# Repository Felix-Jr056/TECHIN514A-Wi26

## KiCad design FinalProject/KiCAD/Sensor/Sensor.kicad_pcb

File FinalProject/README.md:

# ErgoCompass
## Product Idea
ErgoCompass is a product that tracks how you sit using pressure sensors in the back pad and wirelessly sends the data to a desk display. The display converts your posture into a simple status on a physical gauge needle, with an LED alerts when you’ve been slouching for too long. A button on the display device allows calibrating and resets the session.

## Sensor Device
 The sensor device is composed of a fabric back pad with pressure sensors embedded in it. The sensors detect the pressure distribution when a user sits against the pad. The data from the sensors is collected by a microcontroller, which processes the information to determine the user's posture. The device is powered by a rechargeable battery and includes wireless communication capabilities to send the posture data to the desk display.

 Components used in the sensor device include:
 - Pressure Sensors: 3 FSRs (Force Sensitive Resistor).
 - Microcontroller: Custom PCB, may include FSR resistor network, status LED.
 - Wireless Module: For transmitting data to the display device (BLE).
 - Battery: Rechargeable LiPo battery with battery indicator.

| Component name | Model | Quantity |
|----------------|-------|----------|
| Force sensitive resistor | Interlink FSR 406 | 3 |
| Main microcontroller  | Custom PCB | 1 |
| BLE wireless module | Raytac MDBT42Q-512KV2 (nRF52832)| 1 |
| External ADC (optional) | TI ADS1115IDGSR | 1 |
| LiPo battery | 1S LiPo | 1 |
| Status LED | LS R976 | 1 |

## Display Device
The display device receives the posture data from the sensor device and translates it into a visual representation using a physical gauge needle. The needle moves to indicate whether the user's posture is good, moderate, or poor based on the pressure data received. Additionally, the display includes 3 LEDs that displays different colours serving as a pressure level indicator to correct user's posture. A button on the display allows users to calibrate the system and reset their session data.

Components used in the display device include:
- 1 Microcontroller: ESP32.
- 1 Stepper motor driven gauge needle: To visually represent the user's posture.
- 3 LEDs: Indicate the pressure level at each sensor.
- 1 Button: For calibration and session reset functionality.
 - 1 Battery: Small rechargeable LiPo battery.

| Component name | Model | Quantity |
|----------------|-------|----------|
| Microcontroller | XIAO ESP32-C3 | 1 |
| Stepper motor| 28BYJ-48 | 1 |
| LEDs | NeoPixel | 3 |
| Button | Omron B3U-1000P | 1 |
| LiPo battery | 1S LiPo  | 1 |

## Diagrams
### Communication chart

### System Block Diagram

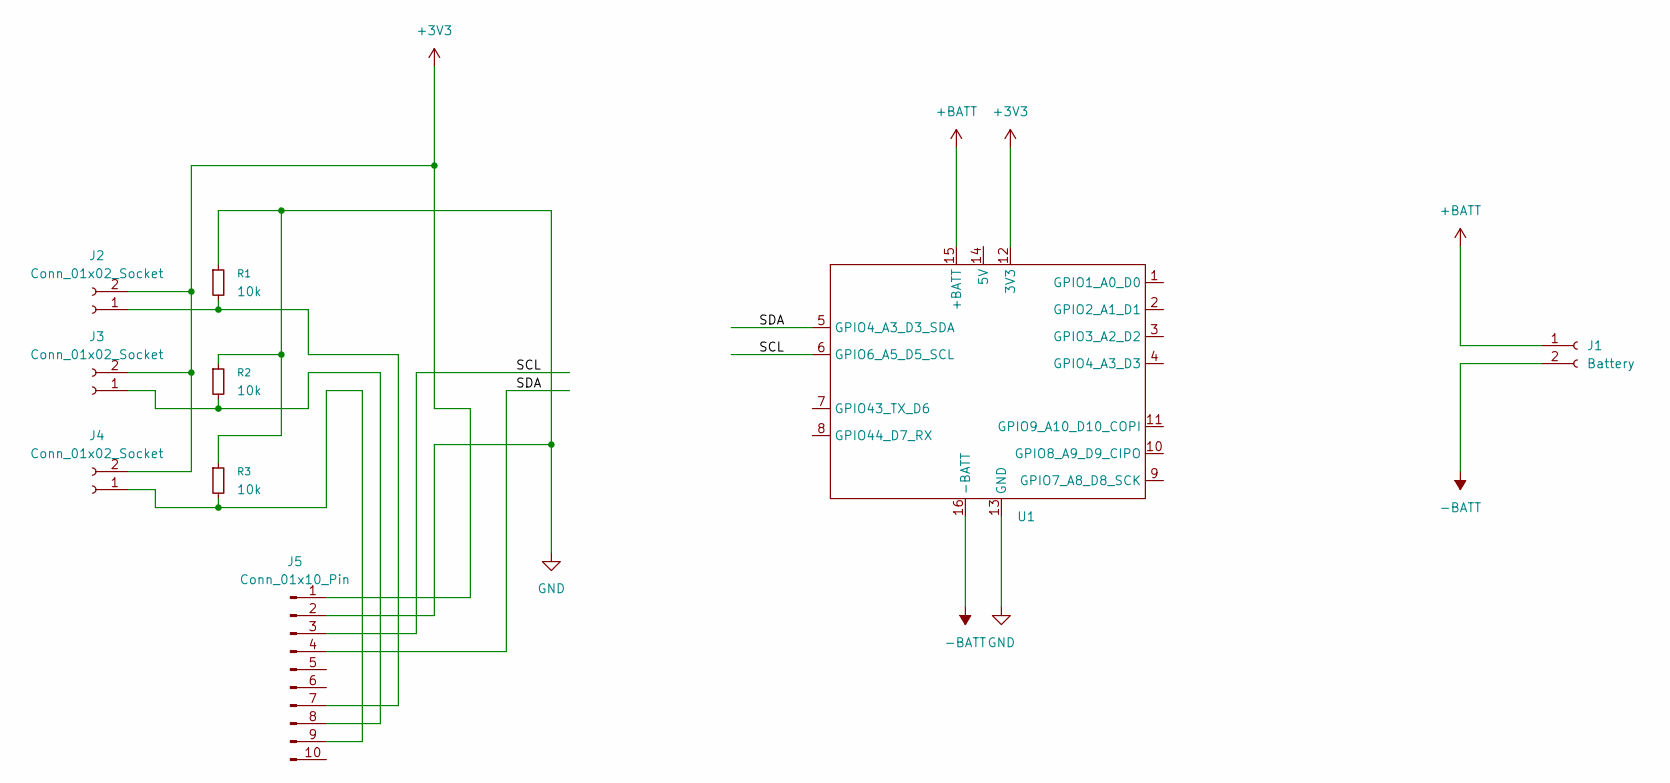
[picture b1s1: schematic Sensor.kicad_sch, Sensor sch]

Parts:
J1: Battery; PinSocket_1x02_P2.54mm_Vertical
J2, J3, J4: Conn_01x02_Socket; PinSocket_1x02_P2.54mm_Vertical
J5: Conn_01x10_Pin; PinHeader_1x10_P2.54mm_Vertical
R1, R2, R3: 10k; R_0805_2012Metric_Pad1.20x1.40mm_HandSolder
U1: XIAO_ESP32

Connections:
+3V3: J2.2, J3.2, J4.2, J5.1, U1.12 (3V3)
+BATT: J1.1, U1.15 (+BATT)
-BATT: J1.2, U1.16 (-BATT)
/SCL: J5.3, U1.6 (GPIO6_A5_D5_SCL)
/SDA: J5.4, U1.5 (GPIO4_A3_D3_SDA)
GND: J5.2, R1.1, R2.1, R3.1, U1.13 (GND)
unnamed: J2.1, J5.7, R1.2
unnamed: J3.1, J5.8, R2.2
unnamed: J4.1, J5.9, R3.2

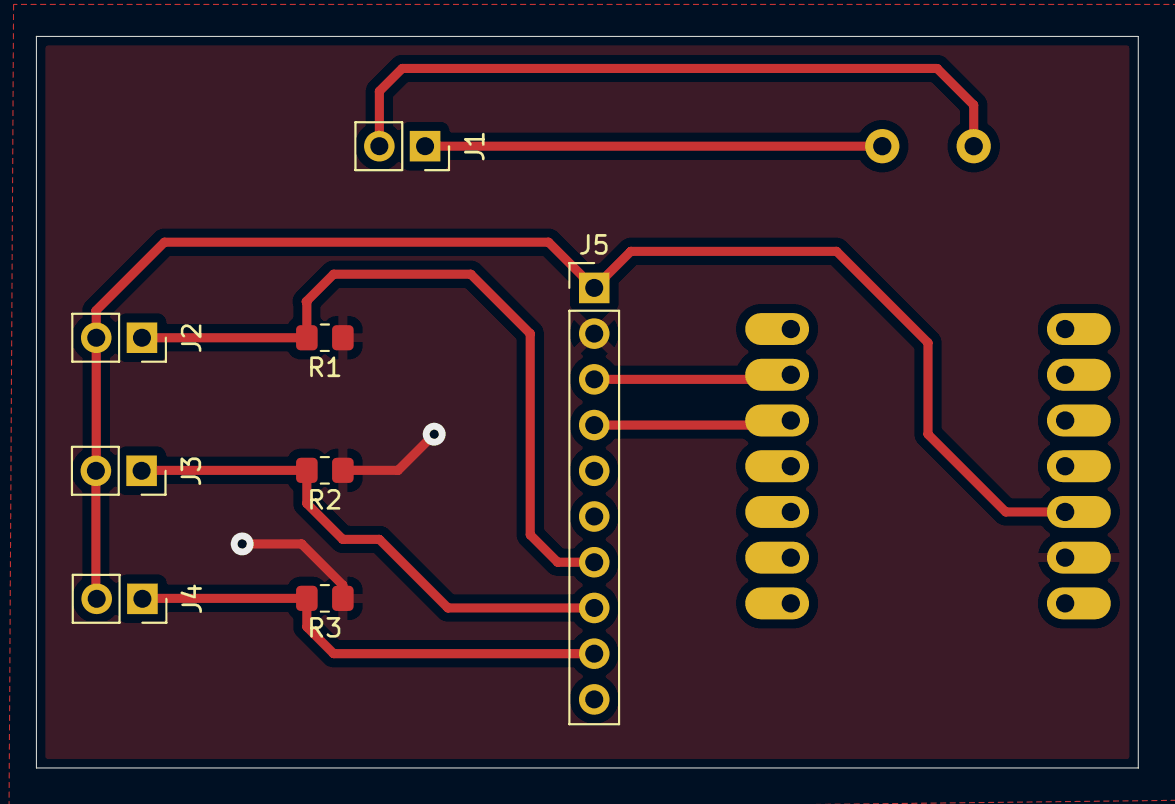
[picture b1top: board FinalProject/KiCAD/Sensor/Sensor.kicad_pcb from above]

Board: 2 copper layers, 61.2 x 40.6 mm, 9 parts (1 on the bottom side), 9 nets.

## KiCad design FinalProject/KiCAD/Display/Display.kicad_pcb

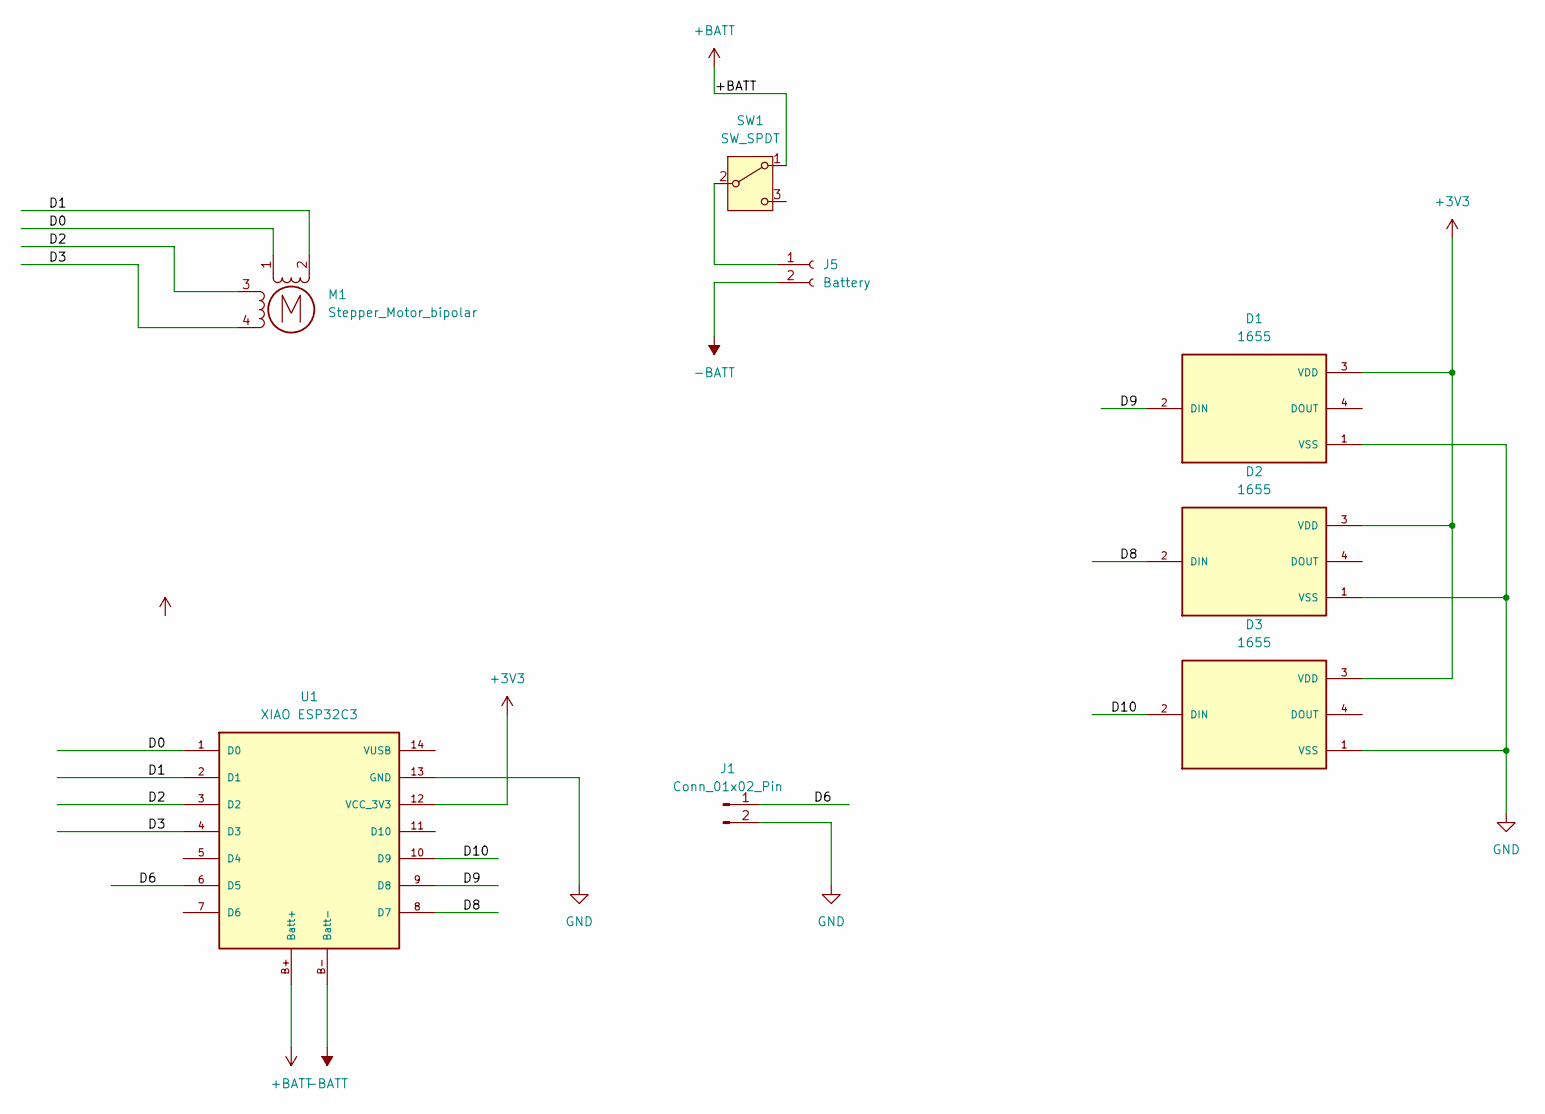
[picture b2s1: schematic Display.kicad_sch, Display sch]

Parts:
D1, D2, D3: 1655; LED_1655; PARTREV 01
J1: Conn_01x02_Pin; PinHeader_1x02_P2.54mm_Vertical
J5: Battery; PinSocket_1x02_P2.54mm_Vertical
M1: Stepper_Motor_bipolar; x27_stepper
SW1: SW_SPDT; PinHeader_1x03_P2.54mm_Vertical
U1: XIAO ESP32C3; NEWxiao_esp32c3

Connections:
+3V3: D1.3 (VDD), D2.3 (VDD), D3.3 (VDD), U1.12 (VCC_3V3)
+BATT: SW1.1 (A), U1.B+ (Batt+)
-BATT: J5.2, U1.B- (Batt-)
/D0: M1.1, U1.1 (D0)
/D1: M1.2 (-), U1.2 (D1)
/D2: M1.3, U1.3 (D2)
/D3: M1.4, U1.4 (D3)
/D6: J1.1, U1.6 (D5)
/D8: D2.2 (DIN), U1.8 (D7)
/D9: D1.2 (DIN), U1.9 (D8)
/D10: D3.2 (DIN), U1.10 (D9)
GND: D1.1 (VSS), D2.1 (VSS), D3.1 (VSS), J1.2, U1.13 (GND)
unnamed: J5.1, SW1.2 (B)

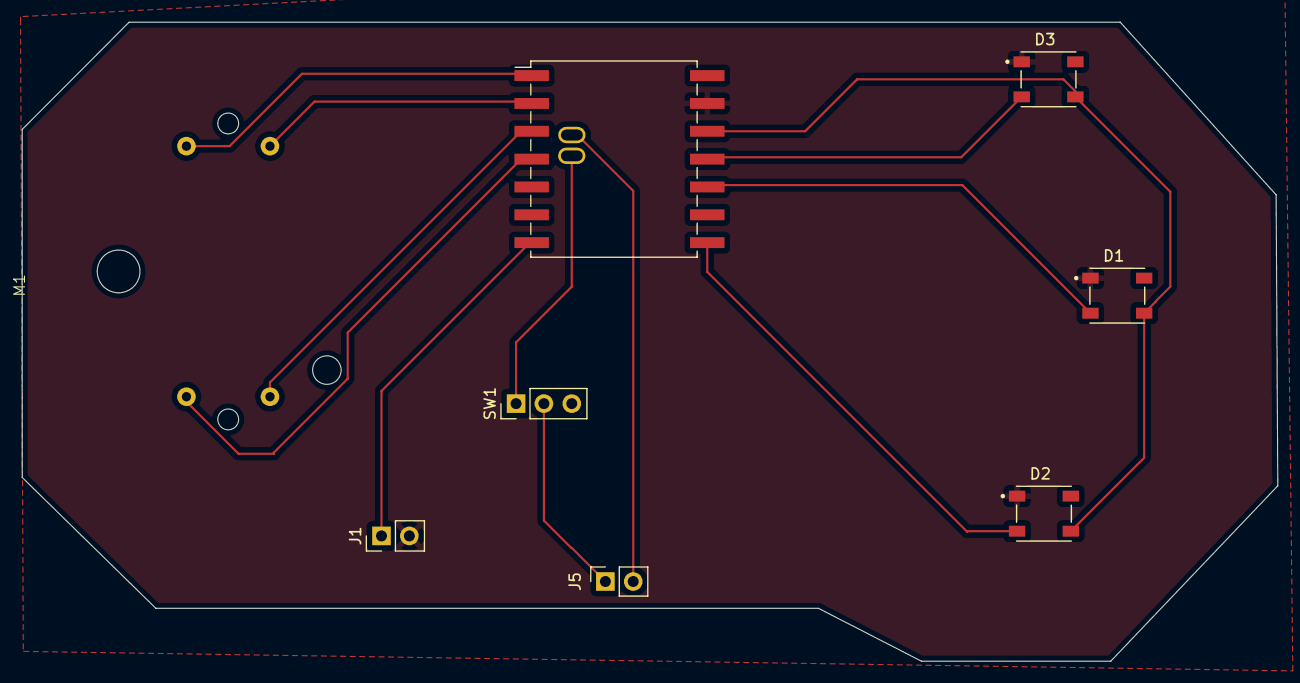
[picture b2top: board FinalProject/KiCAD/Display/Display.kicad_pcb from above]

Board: 2 copper layers, 114.6 x 58.3 mm, 8 parts (0 on the bottom side), 13 nets.

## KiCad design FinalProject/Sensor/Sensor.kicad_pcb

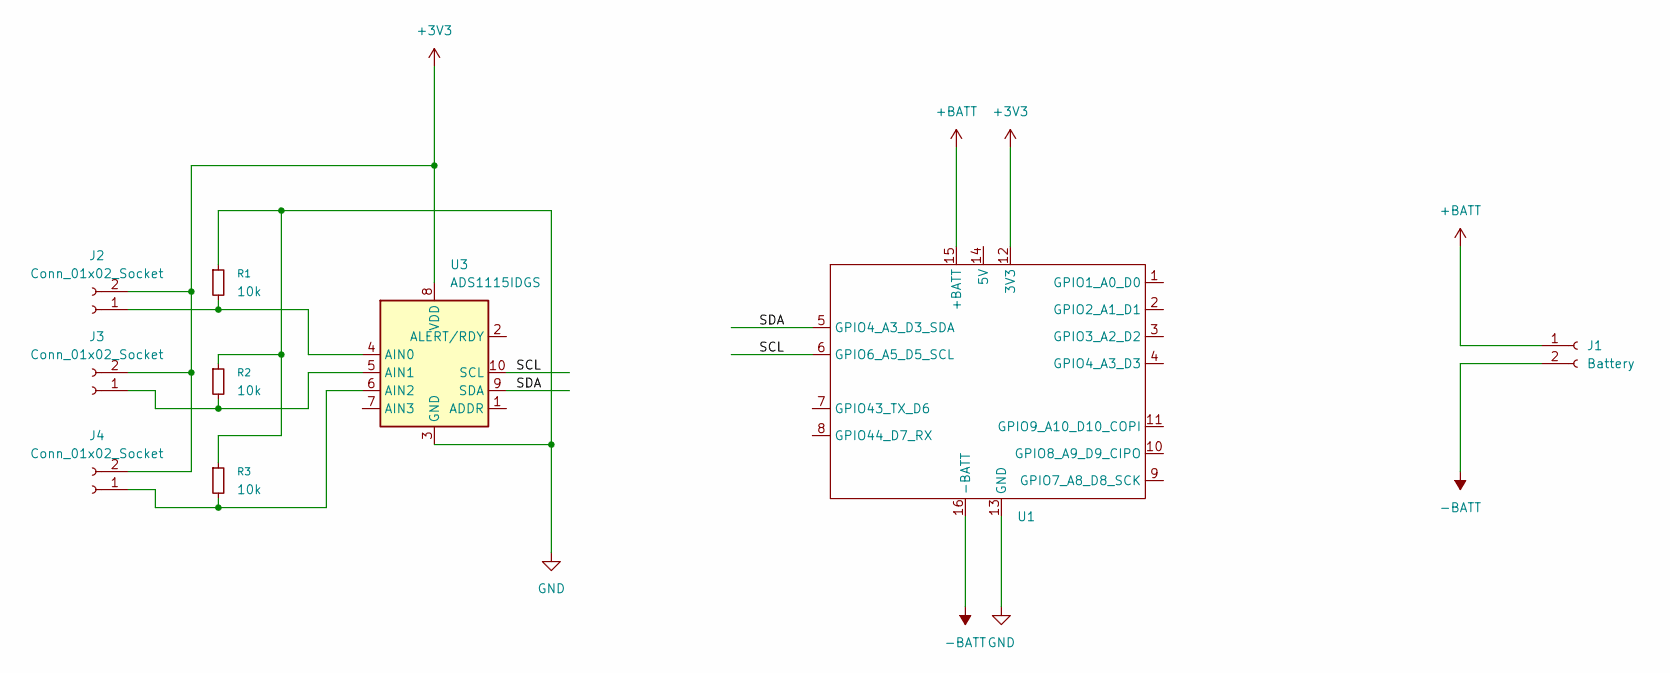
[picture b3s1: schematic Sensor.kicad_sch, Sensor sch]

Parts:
J1: Battery; PinSocket_1x02_P1.00mm_Vertical
J2, J3, J4: Conn_01x02_Socket; PinSocket_1x02_P1.00mm_Vertical
R1, R2, R3: 10k; R_0805_2012Metric_Pad1.20x1.40mm_HandSolder
U1: XIAO_ESP32
U3: ADS1115IDGS; TSSOP-10_3x3mm_P0.5mm

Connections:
+3V3: J2.2, J3.2, J4.2, U1.12 (3V3), U3.8 (VDD)
+BATT: J1.1, U1.15 (+BATT)
-BATT: J1.2, U1.16 (-BATT)
/SCL: U1.6 (GPIO6_A5_D5_SCL), U3.10 (SCL)
/SDA: U1.5 (GPIO4_A3_D3_SDA), U3.9 (SDA)
GND: R1.1, R2.1, R3.1, U1.13 (GND), U3.3 (GND)
unnamed: J2.1, R1.2, U3.4 (AIN0)
unnamed: J3.1, R2.2, U3.5 (AIN1)
unnamed: J4.1, R3.2, U3.6 (AIN2)

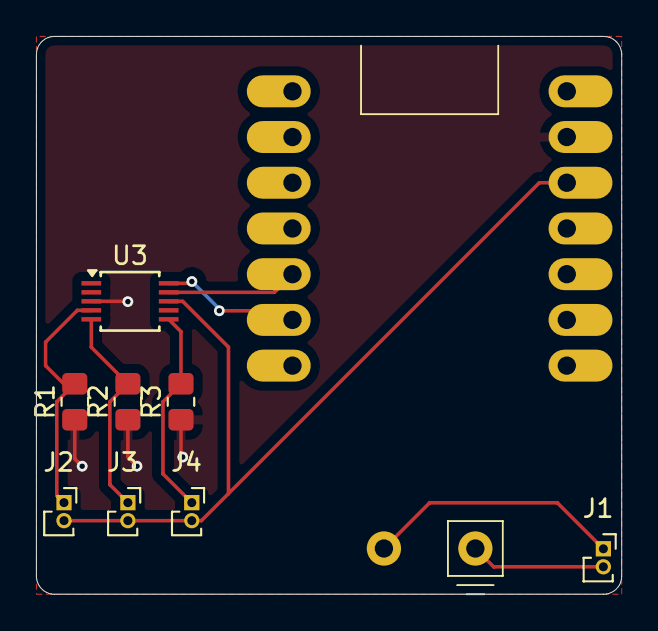
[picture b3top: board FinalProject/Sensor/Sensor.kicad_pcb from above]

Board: 2 copper layers, 32.5 x 31.0 mm, 9 parts (0 on the bottom side), 9 nets.

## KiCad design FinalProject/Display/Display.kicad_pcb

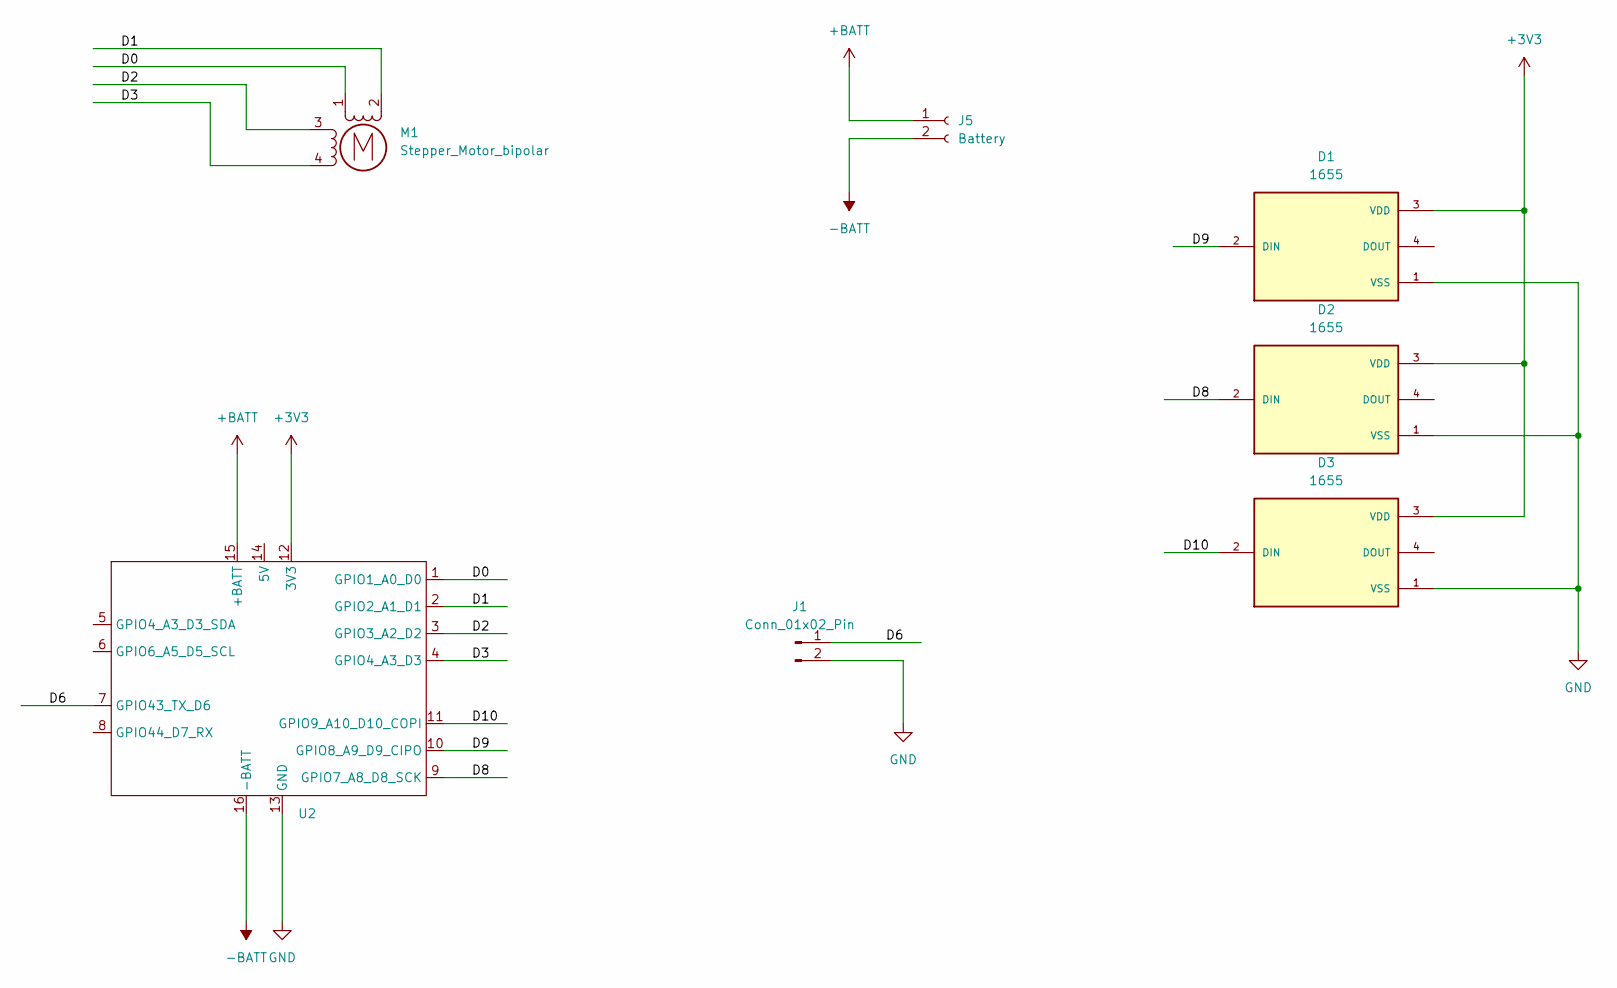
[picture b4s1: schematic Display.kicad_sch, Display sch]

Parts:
D1, D2, D3: 1655; LED_1655; PARTREV 01
J1: Conn_01x02_Pin; PinHeader_1x02_P1.00mm_Vertical
J5: Battery; PinSocket_1x02_P1.00mm_Vertical
M1: Stepper_Motor_bipolar; x27_stepper
U2: XIAO_ESP32

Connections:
+3V3: D1.3 (VDD), D2.3 (VDD), D3.3 (VDD), U2.12 (3V3)
+BATT: J5.1, U2.15 (+BATT)
-BATT: J5.2, U2.16 (-BATT)
/D0: M1.1, U2.1 (GPIO1_A0_D0)
/D1: M1.2 (-), U2.2 (GPIO2_A1_D1)
/D2: M1.3, U2.3 (GPIO3_A2_D2)
/D3: M1.4, U2.4 (GPIO4_A3_D3)
/D6: J1.1, U2.7 (GPIO43_TX_D6)
/D8: D2.2 (DIN), U2.9 (GPIO7_A8_D8_SCK)
/D9: D1.2 (DIN), U2.10 (GPIO8_A9_D9_CIPO)
/D10: D3.2 (DIN), U2.11 (GPIO9_A10_D10_COPI)
GND: D1.1 (VSS), D2.1 (VSS), D3.1 (VSS), J1.2, U2.13 (GND)

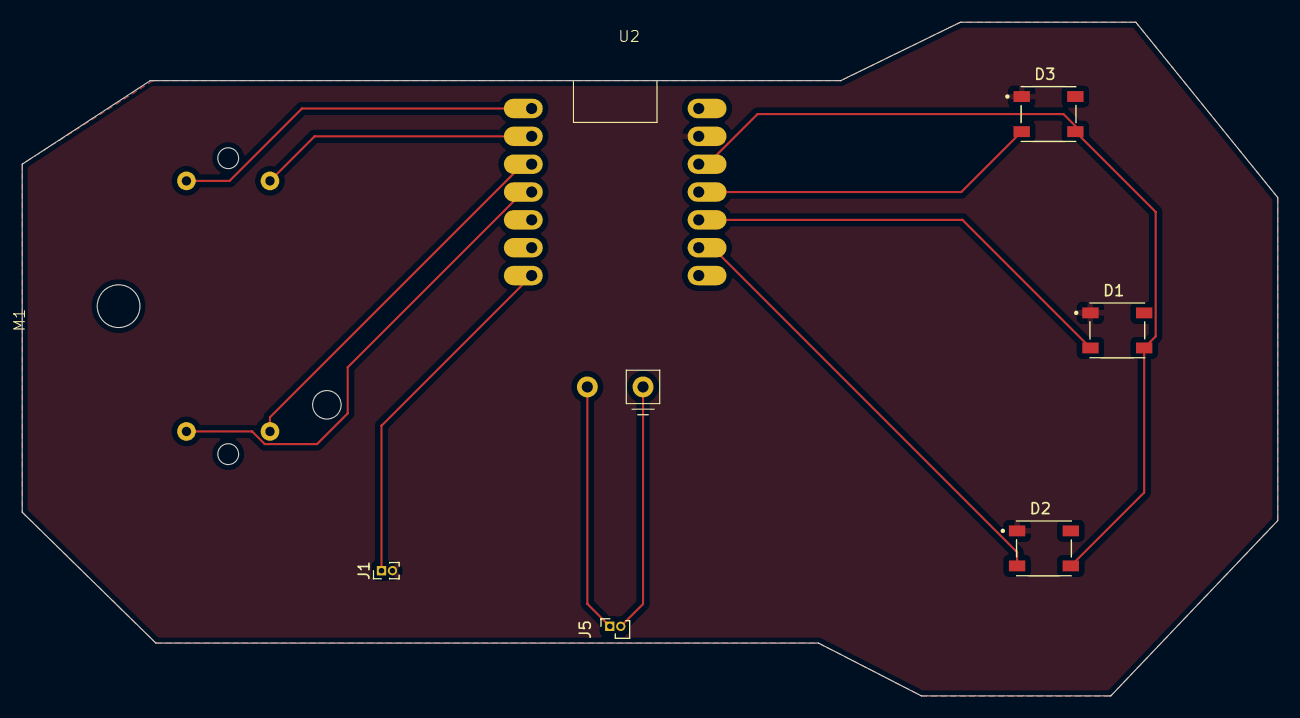
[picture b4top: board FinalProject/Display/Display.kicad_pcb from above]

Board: 2 copper layers, 114.6 x 61.5 mm, 7 parts (0 on the bottom side), 12 nets.

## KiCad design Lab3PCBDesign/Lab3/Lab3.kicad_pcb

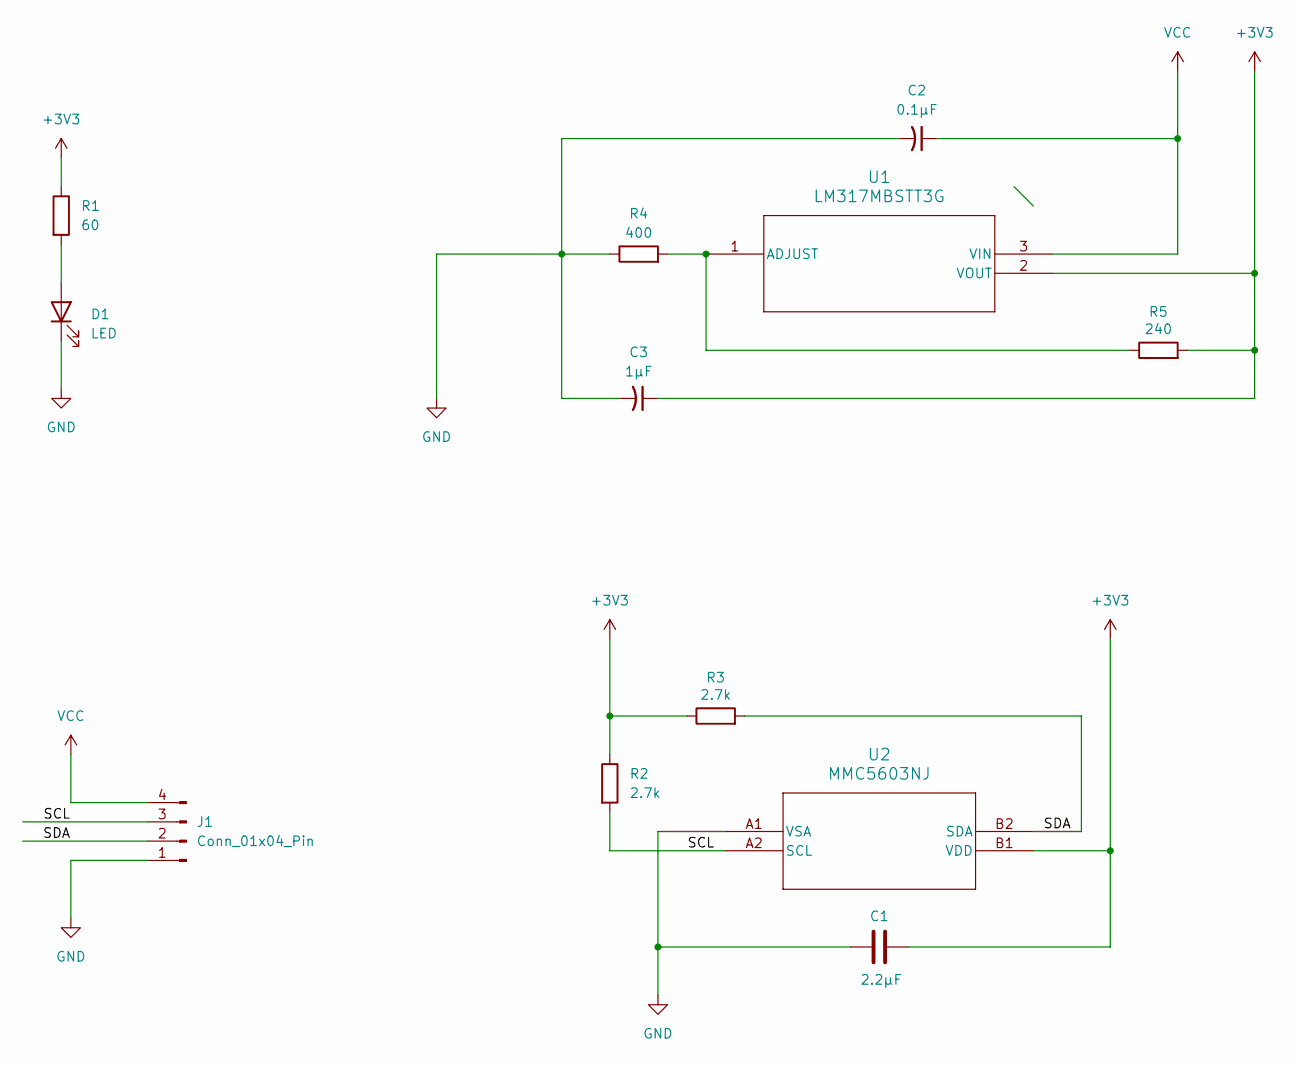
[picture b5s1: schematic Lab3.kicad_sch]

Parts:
C1: 2.2µF; C_0603_1608Metric_Pad1.08x0.95mm_HandSolder
C2: 0.1µF; C_0603_1608Metric_Pad1.08x0.95mm_HandSolder
C3: 1µF; C_0603_1608Metric_Pad1.08x0.95mm_HandSolder
D1: LED; LED_0603_1608Metric_Pad1.05x0.95mm_HandSolder
J1: Conn_01x04_Pin; PinHeader_1x04_P1.00mm_Vertical
R1: 60; R_0603_1608Metric_Pad0.98x0.95mm_HandSolder
R2, R3: 2.7k; R_0603_1608Metric_Pad0.98x0.95mm_HandSolder
R4: 400; R_0603_1608Metric_Pad0.98x0.95mm_HandSolder
R5: 240; R_0603_1608Metric_Pad0.98x0.95mm_HandSolder
U1: LM317MBSTT3G; SOT223-3_ONS
U2: MMC5603NJ; WLP4_0P82X0P82_MEM-L

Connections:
+3V3: C1.2, C3.1, R1.1, R2.1, R3.1, R5.2, U1.2 (VOUT), U2.B1 (VDD)
/SCL: J1.3, R2.2, U2.A2 (SCL)
/SDA: J1.2, R3.2, U2.B2 (SDA)
GND: C1.1, C2.2, C3.2, D1.1 (K), J1.1, R4.1, U2.A1 (VSA)
unnamed: D1.2 (A), R1.2
unnamed: R4.2, R5.1, U1.1 (ADJUST)
VCC: C2.1, J1.4, U1.3 (VIN)

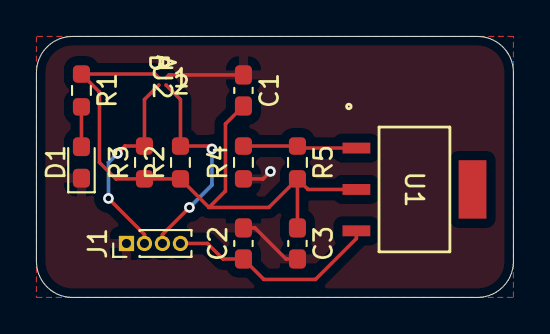
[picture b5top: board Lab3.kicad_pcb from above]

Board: 2 copper layers, 26.5 x 14.5 mm, 12 parts (0 on the bottom side), 7 nets.

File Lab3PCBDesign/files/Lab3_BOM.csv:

"#","Reference","Qty","Value","Footprint","DNP"
"1","C1","1","2.2µF","Capacitor_SMD:C_0603_1608Metric_Pad1.08x0.95mm_HandSolder",""
"2","C2","1","0.1µF","Capacitor_SMD:C_0603_1608Metric_Pad1.08x0.95mm_HandSolder",""
"3","C3","1","1µF","Capacitor_SMD:C_0603_1608Metric_Pad1.08x0.95mm_HandSolder",""
"4","D1","1","LED","LED_SMD:LED_0603_1608Metric_Pad1.05x0.95mm_HandSolder",""
"5","J1","1","Conn_01x04_Pin","Connector_PinHeader_1.00mm:PinHeader_1x04_P1.00mm_Vertical",""
"6","R1","1","60","Resistor_SMD:R_0603_1608Metric_Pad0.98x0.95mm_HandSolder",""
"7","R2, R3","2","2.7k","Resistor_SMD:R_0603_1608Metric_Pad0.98x0.95mm_HandSolder",""
"8","R4","1","400","Resistor_SMD:R_0603_1608Metric_Pad0.98x0.95mm_HandSolder",""
"9","R5","1","240","Resistor_SMD:R_0603_1608Metric_Pad0.98x0.95mm_HandSolder",""
"10","U1","1","LM317MBSTT3G","footprints:SOT223-3_ONS",""
"11","U2","1","MMC5603NJ","footprints:WLP4_0P82X0P82_MEM-L",""

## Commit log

2026-01-05 Lab1 PlatformIO
2026-01-05 L1v1
2026-01-05 Rename Serial Monitor.png to Serial Monitor2.png
2026-01-15 Lab2
2026-01-18 Create Final Project Folder
    Previous three ideas
2026-01-18 Update Name
2026-01-18 Add README
2026-01-19 add gitignore
2026-01-19 All text
2026-01-20 Update datasheet
2026-01-20 Add figures
2026-01-20 Update README figure file path
2026-01-20 Update README component chart
2026-01-20 Add sketch files
2026-01-26 Add KiCad Files
2026-01-27 Update KiCad
2026-01-28 Lab4
2026-01-28 Update files and names of Lab4
2026-01-30 Add Lab3
2026-01-30 Update Lab3
2026-02-05 Lab5
2026-02-05 Add pdf
2026-02-09 Battery Life Estimate
2026-02-12 Lab6
2026-03-01 initial code
2026-03-01 Organize
2026-03-16 Code
